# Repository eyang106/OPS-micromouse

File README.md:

# OPS-micromouse
Capstone for the 2018-2019 UCLA IEEE Open Project Space Program. 

The mouse implements a PID control system to navigate a path defined by walls.

Contents:
- PID control system for the mouse
- Board files and schematic for the distance sensor used

Note: To view the schematic/board, you must download the repo and open the files with EAGLE.

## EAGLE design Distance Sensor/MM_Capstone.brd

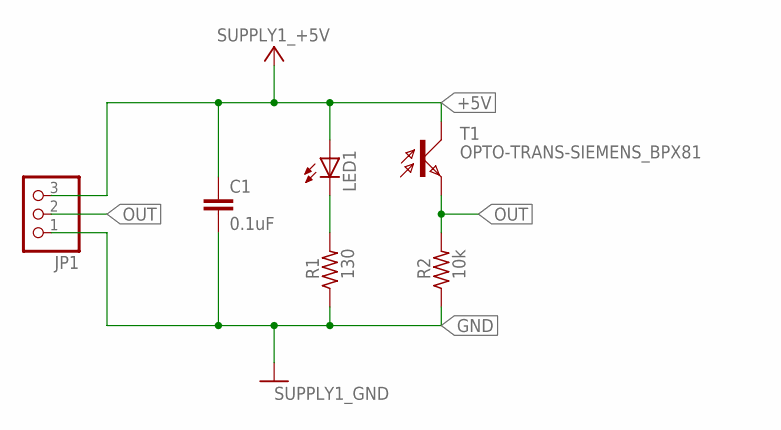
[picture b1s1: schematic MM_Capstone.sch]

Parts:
C1: 0.1uF; RCL_C1206
JP1: PINHEAD_PINHD-1X3; PINHEAD_1X03
LED1: LED_LED5MM
R1: 130; RCL_R1206
R2: 10k; RCL_R1206
T1: OPTO-TRANS-SIEMENS_BPX81

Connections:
+5V: C1.1, JP1.3, LED1.A, T1.C
GND: C1.2, JP1.1, R1.1, R2.1
unnamed: LED1.K (C), R1.2
OUT: JP1.2, R2.2, T1.E

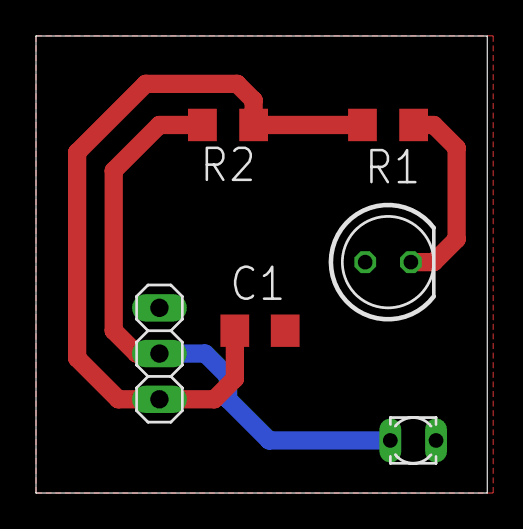
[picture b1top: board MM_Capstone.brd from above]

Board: 2 copper layers, 25.1 x 25.4 mm, 6 parts (0 on the bottom side), 4 nets.
